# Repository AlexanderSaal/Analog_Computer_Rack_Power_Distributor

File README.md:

# Power distrubution board for analog computer rack modules
---

This PCB is a Power-Distribution Board for self designed analog computing modules and are compatilbe with the [THE ANALOG THING (THAT)](https://the-analog-thing.org/) of the [Anabrid](https://anabrid.com/) company. It supplies power, in 16-pin headers, compatible with normal synthezier modules. The **CV** and **Gate** lines can be used as **Mode IC** and **Mode OP** signals to connect the THAT with custom analog cumputing modules. \
Multiple THAT Modules can be daisy chained together through connections on the board. The **Master 1** input supplies the signals **Mode IC** and **Mode OP** which can be connected though jumpers to connected analog computing modules.

---
## PCB render

---
## Schematic

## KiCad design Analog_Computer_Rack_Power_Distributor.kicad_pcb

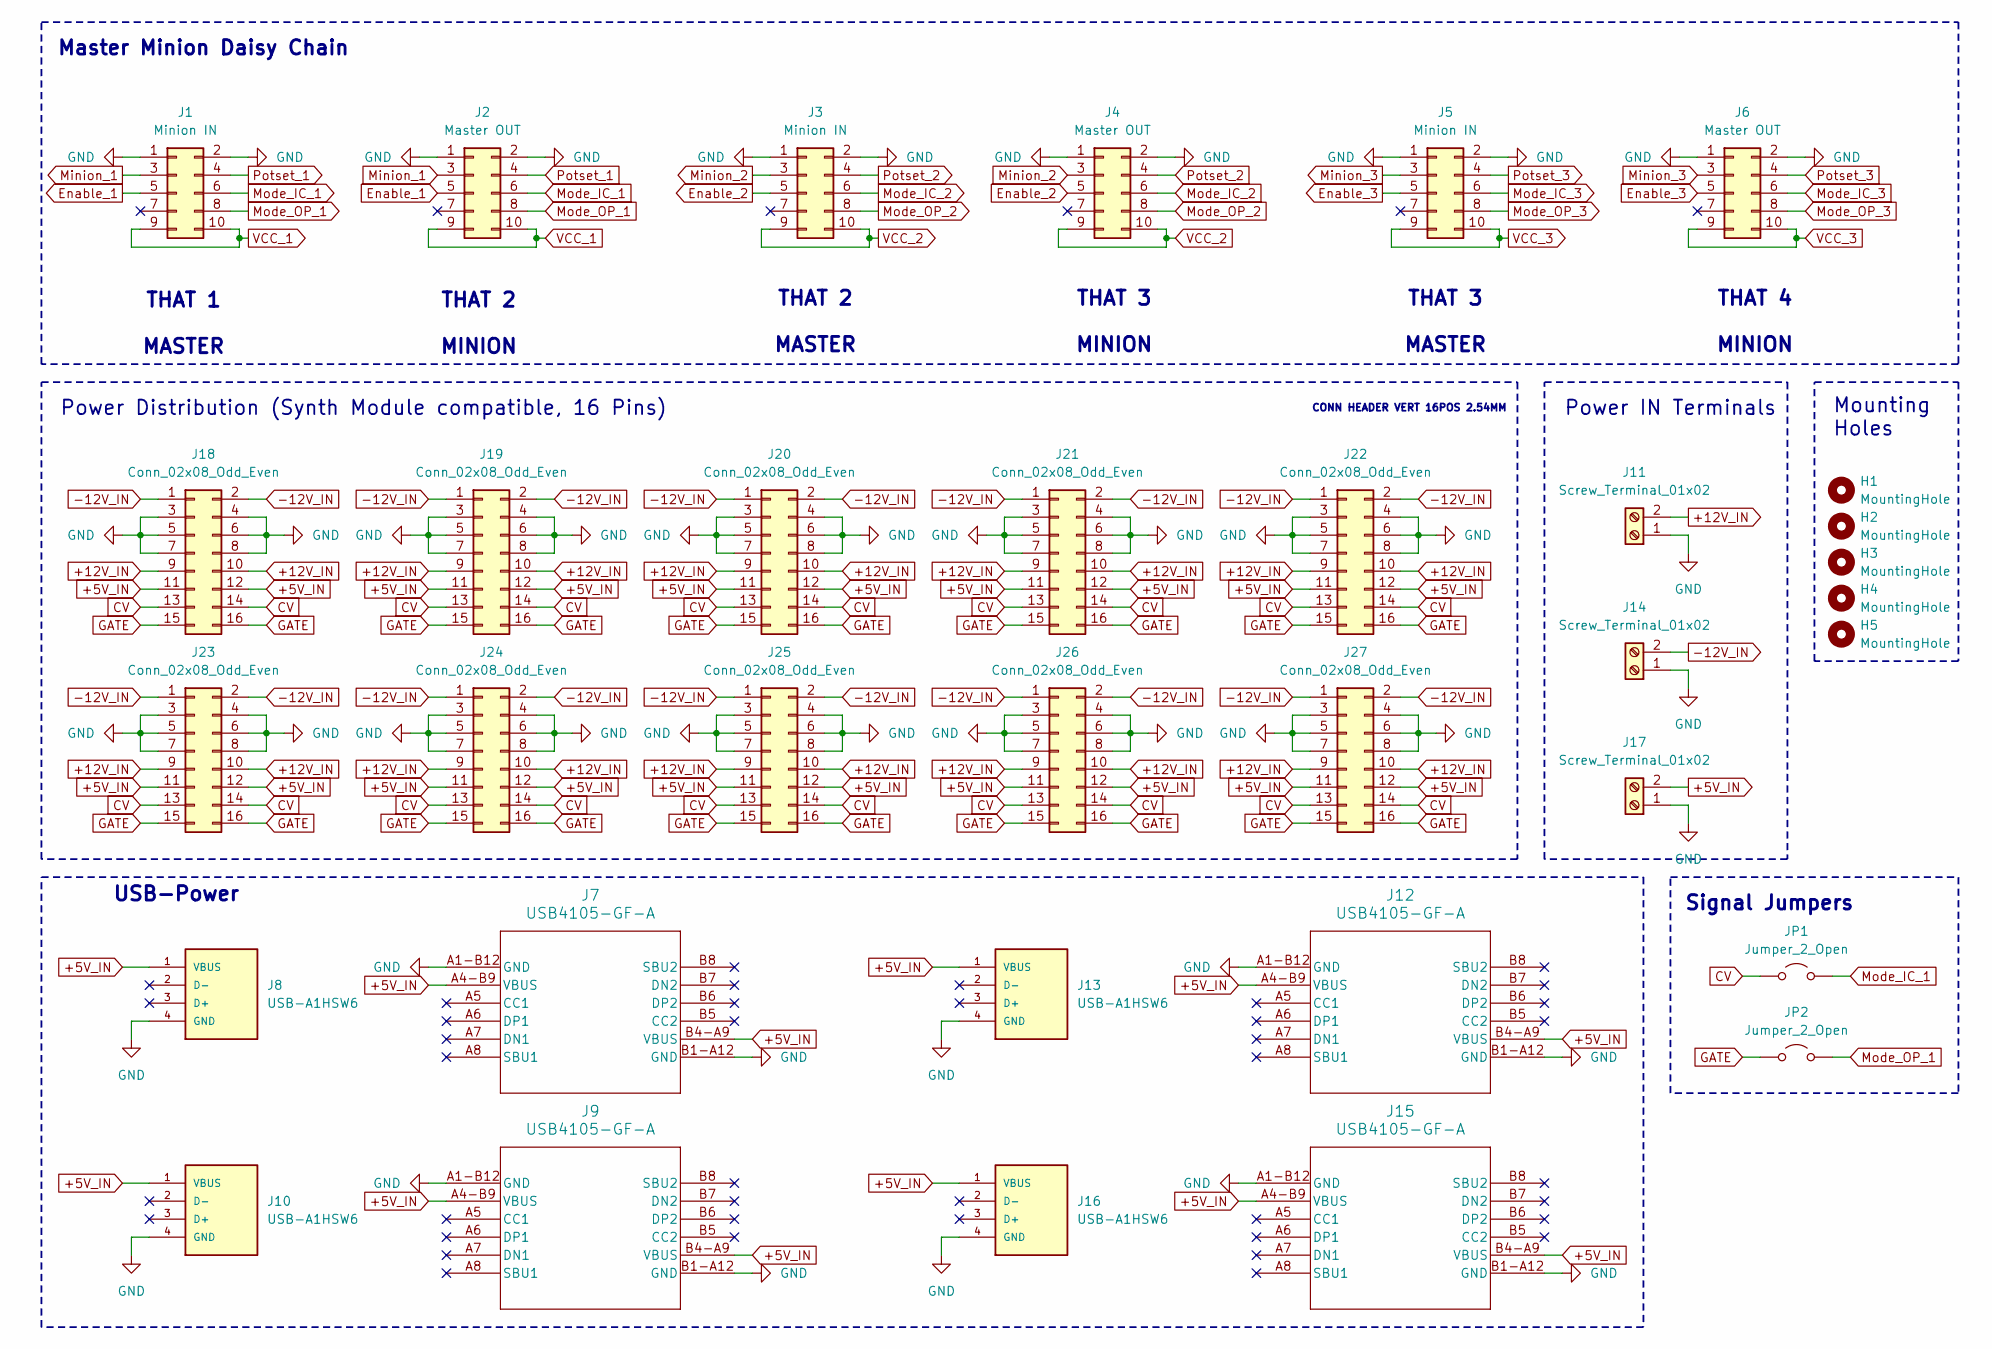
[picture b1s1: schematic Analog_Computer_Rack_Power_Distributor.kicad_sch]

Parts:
H1, H2, H3, H4, H5: MountingHole; MountingHole_3.2mm_M3_DIN965
J1, J3, J5: Minion IN; PinSocket_2x05_P2.54mm_Vertical
J2, J4, J6: Master OUT; PinSocket_2x05_P2.54mm_Vertical
J7, J9, J12, J15: USB4105-GF-A; USB4105_GCT
J8, J10, J13, J16: USB-A1HSW6; OST_USB-A1HSW6; PARTREV A
J11, J14, J17: Screw_Terminal_01x02; TerminalBlock_TB003-500-P02BE
J18, J19, J20, J21, J22, J23, J24, J25, J26, J27: Conn_02x08_Odd_Even; PinHeader_2x08_P2.54mm_Vertical
JP1, JP2: Jumper_2_Open; SolderJumper-2_P1.3mm_Open_TrianglePad1.0x1.5mm

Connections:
+5V_IN: J7.A4-B9 (VBUS), J7.B4-A9 (VBUS), J8.1 (VBUS), J9.A4-B9 (VBUS), J9.B4-A9 (VBUS), J10.1 (VBUS), J12.A4-B9 (VBUS), J12.B4-A9 (VBUS), J13.1 (VBUS), J15.A4-B9 (VBUS), J15.B4-A9 (VBUS), J16.1 (VBUS), J17.2, J18.11, J18.12, J19.11, J19.12, J20.11, J20.12, J21.11, J21.12, J22.11, J22.12, J23.11, J23.12, J24.11, J24.12, J25.11, J25.12, J26.11, J26.12, J27.11, J27.12
+12V_IN: J11.2, J18.9, J18.10, J19.9, J19.10, J20.9, J20.10, J21.9, J21.10, J22.9, J22.10, J23.9, J23.10, J24.9, J24.10, J25.9, J25.10, J26.9, J26.10, J27.9, J27.10
-12V_IN: J14.2, J18.1, J18.2, J19.1, J19.2, J20.1, J20.2, J21.1, J21.2, J22.1, J22.2, J23.1, J23.2, J24.1, J24.2, J25.1, J25.2, J26.1, J26.2, J27.1, J27.2
CV: J18.13, J18.14, J19.13, J19.14, J20.13, J20.14, J21.13, J21.14, J22.13, J22.14, J23.13, J23.14, J24.13, J24.14, J25.13, J25.14, J26.13, J26.14, J27.13, J27.14, JP1.1 (A)
Enable_1: J1.5, J2.5
Enable_2: J3.5, J4.5
Enable_3: J5.5, J6.5
GATE: J18.15, J18.16, J19.15, J19.16, J20.15, J20.16, J21.15, J21.16, J22.15, J22.16, J23.15, J23.16, J24.15, J24.16, J25.15, J25.16, J26.15, J26.16, J27.15, J27.16, JP2.1 (A)
GND: J1.1, J1.2, J2.1, J2.2, J3.1, J3.2, J4.1, J4.2, J5.1, J5.2, J6.1, J6.2, J7.A1-B12 (GND), J7.B1-A12 (GND), J8.4 (GND), J9.A1-B12 (GND), J9.B1-A12 (GND), J10.4 (GND), J11.1, J12.A1-B12 (GND), J12.B1-A12 (GND), J13.4 (GND), J14.1, J15.A1-B12 (GND), J15.B1-A12 (GND), J16.4 (GND), J17.1, J18.3, J18.4, J18.5, J18.6, J18.7, J18.8, J19.3, J19.4, J19.5, J19.6, J19.7, J19.8, J20.3, J20.4, J20.5, J20.6, J20.7, J20.8, J21.3, J21.4, J21.5, J21.6, J21.7, J21.8, J22.3, J22.4, J22.5, J22.6, J22.7, J22.8, J23.3, J23.4, J23.5, J23.6, J23.7, J23.8, J24.3, J24.4, J24.5, J24.6, J24.7, J24.8, J25.3, J25.4, J25.5, J25.6, J25.7, J25.8, J26.3, J26.4, J26.5, J26.6, J26.7, J26.8, J27.3, J27.4, J27.5, J27.6, J27.7, J27.8
Minion_1: J1.3, J2.3
Minion_2: J3.3, J4.3
Minion_3: J5.3, J6.3
Mode_IC_1: J1.6, J2.6, JP1.2 (B)
Mode_IC_2: J3.6, J4.6
Mode_IC_3: J5.6, J6.6
Mode_OP_1: J1.8, J2.8, JP2.2 (B)
Mode_OP_2: J3.8, J4.8
Mode_OP_3: J5.8, J6.8
Potset_1: J1.4, J2.4
Potset_2: J3.4, J4.4
Potset_3: J5.4, J6.4
VCC_1: J1.9, J1.10, J2.9, J2.10
VCC_2: J3.9, J3.10, J4.9, J4.10
VCC_3: J5.9, J5.10, J6.9, J6.10

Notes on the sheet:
THAT 3 MINION
Master Minion Daisy Chain
Signal Jumpers
THAT 2 MINION
THAT 3 MASTER
THAT 1 MASTER
CONN HEADER VERT 16POS 2.54MM
USB-Power
Mounting Holes
Power Distribution (Synth Module compatible, 16 Pins)
Power IN Terminals
THAT 2 MASTER
THAT 4 MINION

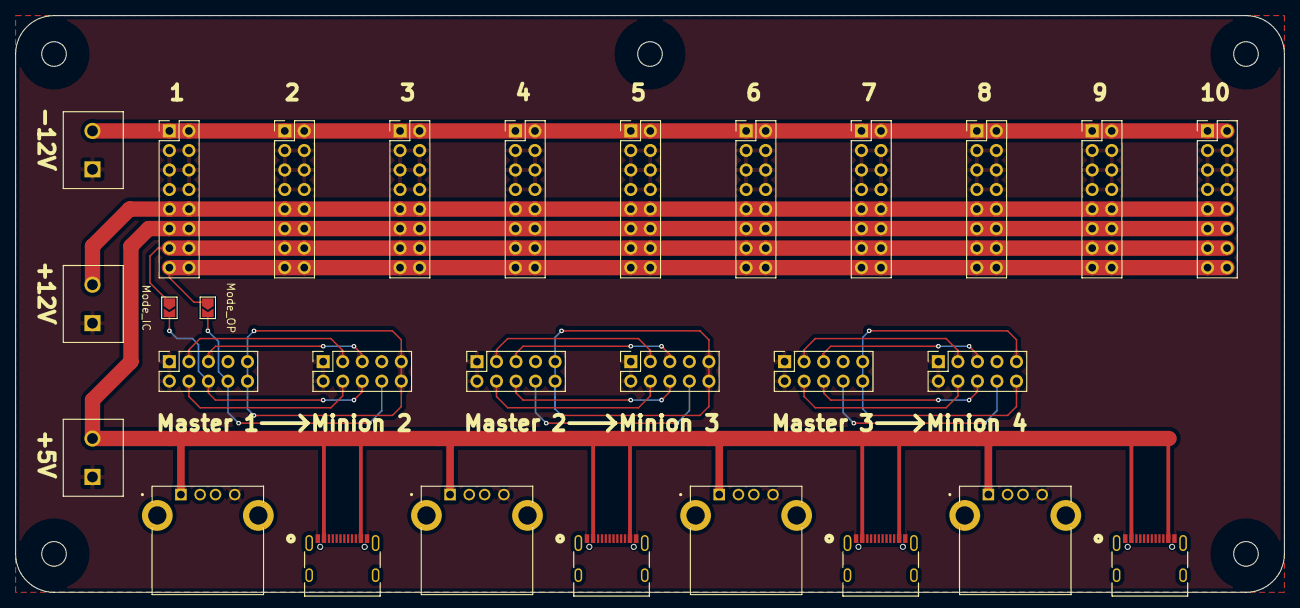
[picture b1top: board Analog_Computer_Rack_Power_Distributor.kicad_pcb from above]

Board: 2 copper layers, 165.0 x 75.0 mm, 34 parts (0 on the bottom side), 24 nets.

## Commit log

2024-10-03 finished V1
2024-10-03 Create LICENSE
